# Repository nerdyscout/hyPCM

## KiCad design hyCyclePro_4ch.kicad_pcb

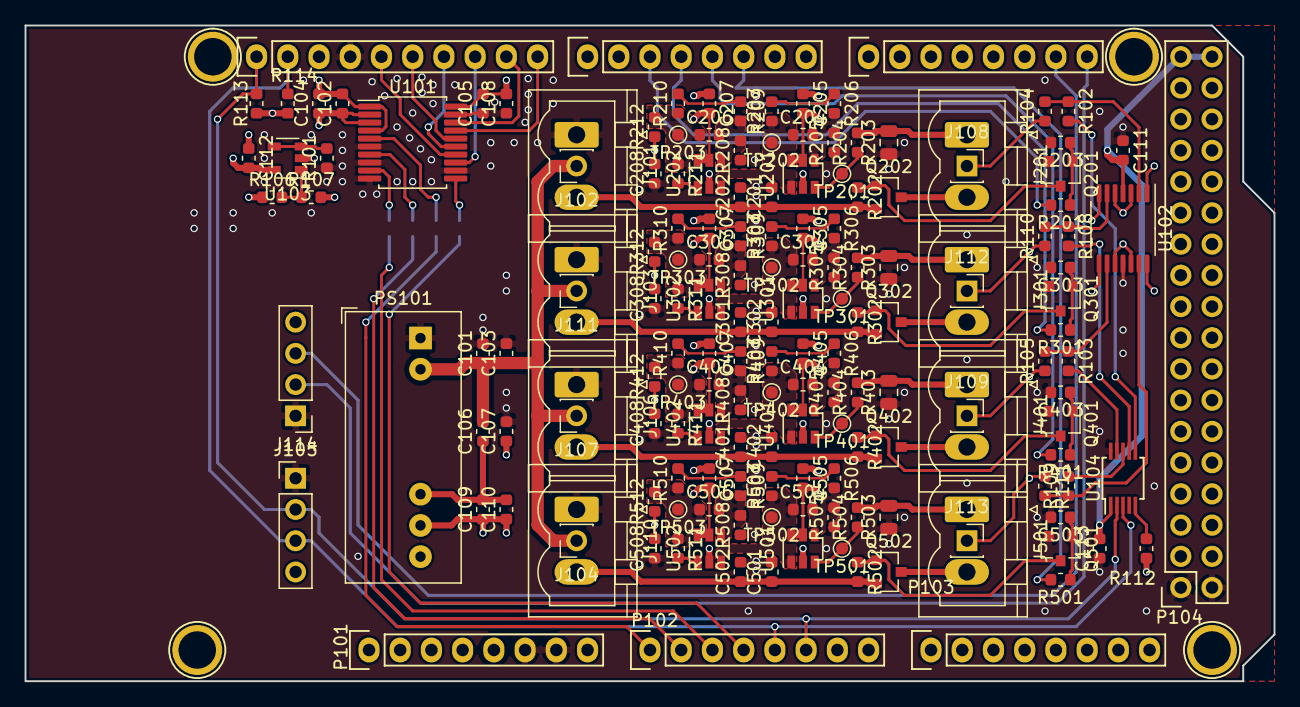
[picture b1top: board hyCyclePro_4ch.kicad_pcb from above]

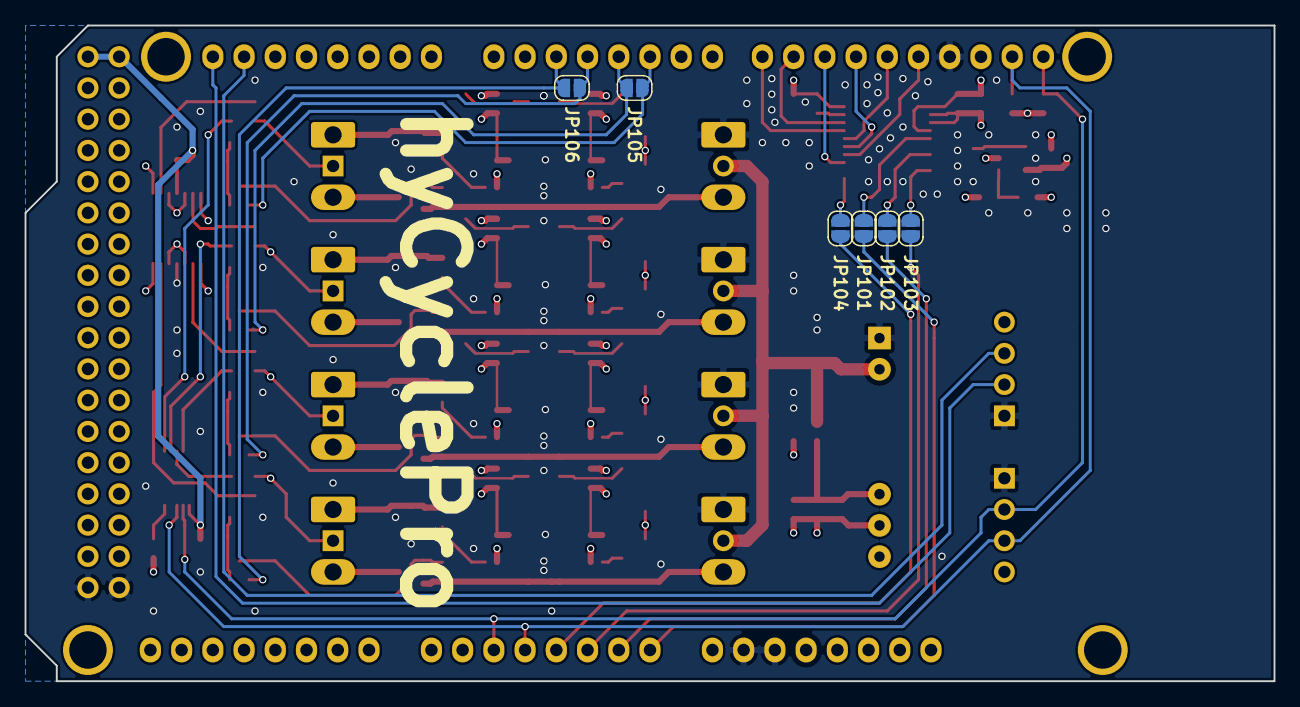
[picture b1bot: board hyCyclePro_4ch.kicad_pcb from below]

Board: 4 copper layers, 101.6 x 53.3 mm, 175 parts (6 on the bottom side), 95 nets.

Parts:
C101, C102, C105, C110, C203, C208, C303, C308, C403, C408, C503, C508: 10n; C_0603_1608Metric
C103, C109: 10µ; C_0603_1608Metric
C104, C108, C111, C112, C113, C205, C305, C405, C505: 100n; C_0603_1608Metric
C106, C107, C201, C202, C207, C301, C302, C307, C401, C402, C407, C501, C502, C507: DNP; C_0603_1608Metric
C204, C206, C304, C306, C404, C406, C504, C506: 10p; C_0603_1608Metric
J101, J103, J106, J110: Conn_01x02; PhoenixContact_MSTBVA_2,5_2-G-5,08_1x02_P5.08mm_Vertical
J102, J104, J107, J108, J109, J111, J112, J113: Conn_01x01; PinSocket_1x01_P2.54mm_Vertical
J105: TWI0; PinHeader_1x04_P2.54mm_Vertical
J114: TWI1; PinHeader_1x04_P2.54mm_Vertical
J201, J301, J401, J501: DUT; PhoenixContact_MSTBVA_2,5_2-G-5,08_1x02_P5.08mm_Vertical
JP101, JP102, JP103, JP104, JP105, JP106: Jumper_SolderJumper_2_Open; SolderJumper-2_P1.3mm_Open_RoundedPad1.0x1.5mm
P101: Power; Socket_Strip_Arduino_1x08
P102: Analog; Socket_Strip_Arduino_1x08
P103: GPIO; Socket_Strip_Arduino_1x08
P104: Digital; Socket_Strip_Arduino_2x18
P105: Serial; Socket_Strip_Arduino_1x10
P106: Timer; Socket_Strip_Arduino_1x08
P107: Serial; Socket_Strip_Arduino_1x08
P108, P109, P110, P111: CONN_01X01; Arduino_1pin
PS101: ITX0503SA; Converter_DCDC_XP_POWER-ITXxxxxSA_THT
Q201, Q301, Q401, Q501: IRLML6244; SOT-23
Q202, Q302, Q402, Q502: IRLML6402; SOT-23
R101, R204, R211, R304, R311, R404, R411, R504, R511: 270; R_0603_1608Metric
R102, R103, R108, R109: 120k 1%; R_0603_1608Metric
R104, R105, R110, R111: 200k 1%; R_0603_1608Metric
R106, R107: 100k 1%; R_0603_1608Metric
R112: 100k; R_0603_1608Metric
R113, R114: DNP; R_0603_1608Metric
R201, R301, R401, R501: 470; R_0603_1608Metric
R202, R212, R302, R312, R402, R412, R502, R512: 1k; R_0603_1608Metric
R203, R303, R403, R503: 0.010 0.05%; R_0805_2012Metric
R205, R208, R305, R308, R405, R408, R505, R508: 1k 0.05%; R_0603_1608Metric
R206, R209, R306, R309, R406, R409, R506, R509: 6k8 0.05%; R_0603_1608Metric
R207, R210, R307, R310, R407, R410, R507, R510: 2k2 0.05%; R_0603_1608Metric
TP201, TP202, TP203, TP301, TP302, TP303, TP401, TP402, TP403, TP501, TP502, TP503: TestPoint; TestPoint_Pad_D1.0mm
U101: MCP3564; SSOP-20_5.3x7.2mm_P0.65mm
U102: LM324; TSSOP-14_4.4x5mm_P0.65mm
U103: LMV321; SOT-23-5
U104: MCP4728; MSOP-10_3x3mm_P0.5mm
U201, U202, U301, U302, U401, U402, U501, U502: MAX4239AUT; SOT-23-6

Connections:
+3V3: C111.2, C113.2, J105.4, J114.4, P101.2, P101.4, P104.35, P104.36, R112.1, R113.1, R114.1, U102.4, U104.1
+5V: C101.1, C103.1, C106.2, J102.1, J104.1, J107.1, J111.1, P101.5, PS101.2
/DAC1: R102.2, U104.6
/DAC2: R108.2, U104.7
/DAC3: R109.2, U104.8
/DAC4: R103.2, U104.9
/MCLKIN: P105.9, U101.18
/MDAT: P105.10, U101.17
/RDY: R112.2, U104.5
/TWI1_SCL: J114.2, P107.8
/TWI1_SDA: J114.3, P107.7
/ana0: C208.2, JP101.1, R212.1, U101.5
/ana2: C308.2, JP102.1, R312.1, U101.7
/ana4: C408.2, JP103.1, R412.1, U101.9
/ana6: C508.2, JP104.1, R512.1, U101.11
/ch11: JP105.1, P106.3, R201.2
/ch12: JP105.2, P106.4, R301.2
/ch13: JP106.1, P106.5, R401.2
/ch14: JP106.2, P106.6, R501.2
/d1: J108.1, R104.1, U102.1
/d2: J112.1, R110.1, U102.7
/d3: J109.1, R105.1, U102.8
/d4: J113.1, R111.1, U102.14
/port1/Power: C201.1, C202.1, J101.2, Q202.2, R202.2
/port1/Power+: J201.2, Q202.3
/port1/Power-: J201.1, R203.2, R204.2
/port2/Power: C301.1, C302.1, J103.2, Q302.2, R302.2
/port2/Power+: J301.2, Q302.3
/port2/Power-: J301.1, R303.2, R304.2
/port3/Power: C401.1, C402.1, J106.2, Q402.2, R402.2
/port3/Power+: J401.2, Q402.3
/port3/Power-: J401.1, R403.2, R404.2
/port4/Power: C501.1, C502.1, J110.2, Q502.2, R502.2
/port4/Power+: J501.2, Q502.3
/port4/Power-: J501.1, R503.2, R504.2
GND: C101.2, C103.2, C105.1, C107.2, C108.1, C111.1, C113.1, C201.2, C202.2, C203.2, C208.1, C301.2, C302.2, C303.2, C308.1, C401.2, C402.2, C403.2, C408.1, C501.2, C502.2, C503.2, C508.1, J101.1, J103.1, J105.1, J106.1, J110.1, J114.1, P101.6, P101.7, P104.1, P104.2, P105.4, PS101.1, Q201.2, Q301.2, Q401.2, Q501.2, R101.1, R203.1, R205.1, R208.1, R303.1, R305.1, R308.1, R403.1, R405.1, R408.1, R503.1, R505.1, R508.1, U101.6, U101.8, U101.10, U101.12, U101.19, U102.11, U104.10
GNDA: C102.1, C104.1, C107.1, C109.1, C110.1, C112.1, C205.1, C207.1, C305.1, C307.1, C405.1, C407.1, C505.1, C507.1, PS101.7, R107.2, U101.2, U101.3, U102.3, U102.5, U102.10, U102.12, U103.2, U201.2, U202.2, U301.2, U302.2, U401.2, U402.2, U501.2, U502.2
unnamed: C203.1, Q201.1, R201.1
unnamed: C204.1, R207.1, TP202.1, U201.1, U202.3
unnamed: C204.2, R205.2, R206.2, U201.4
unnamed: C206.1, R210.1, R211.1, R212.2, TP203.1
unnamed: C206.2, R208.2, R209.2, U202.4
unnamed: C303.1, Q301.1, R301.1
unnamed: C304.1, R307.1, TP302.1, U301.1, U302.3
unnamed: C304.2, R305.2, R306.2, U301.4
unnamed: C306.1, R310.1, R311.1, R312.2, TP303.1
unnamed: C306.2, R308.2, R309.2, U302.4
unnamed: C403.1, Q401.1, R401.1
unnamed: C404.1, R407.1, TP402.1, U401.1, U402.3
unnamed: C404.2, R405.2, R406.2, U401.4
unnamed: C406.1, R410.1, R411.1, R412.2, TP403.1
unnamed: C406.2, R408.2, R409.2, U402.4
unnamed: C503.1, Q501.1, R501.1
unnamed: C504.1, R507.1, TP502.1, U501.1, U502.3
unnamed: C504.2, R505.2, R506.2, U501.4
unnamed: C506.1, R510.1, R511.1, R512.2, TP503.1
unnamed: C506.2, R508.2, R509.2, U502.4
unnamed: JP101.2, P102.1
unnamed: JP102.2, P102.2
unnamed: JP103.2, P102.3
unnamed: JP104.2, P102.4
unnamed: Q201.3, Q202.1, R202.1
unnamed: Q301.3, Q302.1, R302.1
unnamed: Q401.3, Q402.1, R402.1
unnamed: Q501.3, Q502.1, R502.1
unnamed: R101.2, U103.3, U103.4
unnamed: R102.1, R104.2, U102.2
unnamed: R103.1, R105.2, U102.9
unnamed: R106.2, R107.1, U103.1
unnamed: R108.1, R110.2, U102.6
unnamed: R109.1, R111.2, U102.13
unnamed: R204.1, TP201.1, U201.3
unnamed: R206.1, R207.2
unnamed: R209.1, R210.2
unnamed: R211.2, U202.1
unnamed: R304.1, TP301.1, U301.3
unnamed: R306.1, R307.2
unnamed: R309.1, R310.2
unnamed: R311.2, U302.1
unnamed: R404.1, TP401.1, U401.3
unnamed: R406.1, R407.2
unnamed: R409.1, R410.2
unnamed: R411.2, U402.1
unnamed: R504.1, TP501.1, U501.3
unnamed: R506.1, R507.2
unnamed: R509.1, R510.2
unnamed: R511.2, U502.1
SPI1_CLK: P105.5, U101.14
SPI1_CS0: P105.8, U101.13
SPI1_MISO: P105.6, U101.16
SPI1_MOSI: P105.7, U101.15
TWI0_SCL: J105.2, P102.6, P105.1, R113.2, U104.2
TWI0_SDA: J105.3, P102.5, P105.2, R114.2, U104.3
VDD: C105.2, C108.2, U101.20
VDDA: C102.2, C104.2, C106.1, C109.2, C110.2, C112.2, C205.2, C207.2, C305.2, C307.2, C405.2, C407.2, C505.2, C507.2, PS101.6, R106.1, U101.1, U101.4, U103.5, U201.5, U201.6, U202.5, U202.6, U301.5, U301.6, U302.5, U302.6, U401.5, U401.6, U402.5, U402.6, U501.5, U501.6, U502.5, U502.6

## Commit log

2021-12-27 add original (but faulty) schematic
2021-12-27 add first draft of board (based on faulty schematic)
2021-12-27 add custom parts from rescue lib
2021-12-27 latest changes
